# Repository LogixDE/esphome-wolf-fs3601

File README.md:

# ESPHome-Ersatz für den Wolf-Fernversteller FS 3601

Ein **ESP32-C3 mit ESPHome** ersetzt die analoge Fernbedienung **Wolf FS 3601** eines alten Wolf-Gaskessels (hier NG-2E-17, Baujahr 1993). Die Platine bildet den Widerstand zwischen den Kesselklemmen 1 und 2 nach, galvanisch getrennt über PhotoMOS-Relais. Damit kann **Home Assistant** die Heizkurve des Kessels stufenlos und **bedarfsgerecht** nachregeln, abhängig davon, was die einzelnen Räume tatsächlich brauchen.

| Original FS 3601 | Ersatzplatine FS3601-ESP |
|---|---|
|  |  |

## Was drin ist

| Ordner | Inhalt |
|---|---|
| [`docs/`](docs) | Dokumentation, Messwerte, Diagramme |
| [`fs3601/`](fs3601) | Reverse-Engineering der Original-FB: Fotos (nummerierte Lötaugen), Schaltplan |
| [`hardware/`](hardware) | KiCad-Platine, Gerber, Stückliste, Bestückungsdaten, Schaltplan, Generator-Skripte |
| [`firmware/`](firmware) | ESPHome-Konfiguration |
| [`home-assistant/`](home-assistant) | Automationen und Helfer für die bedarfsgerechte Heizkurve |
| [`tools/`](tools) | Hilfsskripte (Bildentzerrung, Diagramme) |

## Dokumentation

1. [Reverse-Engineering der FS 3601](docs/1_reverse_engineering.md): Netzliste, Schalterstellungen, Kennfeld
2. [Hardware](docs/2_hardware.md): Platine, Bestückung, galvanische Trennung, Inbetriebnahme, Kalibrierung
3. [Firmware](docs/3_firmware.md): Betriebsarten, Entitäten, Sicherheit
4. [Home Assistant](docs/4_home_assistant.md): bedarfsgerechte Heizkurve, Kesselschutz, erste Ergebnisse
5. [Messwerte](docs/5_messwerte.md): alle Messungen und Lehrgeld

## Kurzfassung

- Der Kessel misst nur den **Widerstand an Klemme 1–2**. Mit Raumeinfluss 0 erzeugt die FS 3601 Werte von **12,96 kΩ bis 16,30 kΩ** sowie 3,87 kΩ für „Aus“.
- Die Platine stellt **64 Widerstandswerte** von 12,88 bis 16,37 kΩ ein (Raster ≤ 70 Ω), über sechs PhotoMOS-Schließer (TLP240A) an einer Widerstandskette. Ein **PhotoMOS-Öffner** (CPC1117N) brückt K1–K2, wenn der ESP stromlos ist. Dann läuft der Kessel wie ohne Fernbedienung.
- Eigenes Netzteil (HLK-PM01) mit Sicherung und Varistor. Zum Kessel hin ist alles über die PhotoMOS getrennt (Klemme 1 liegt auf N).
- In Home Assistant regelt eine Automation die **Heizkurve 0–100 %** alle 10 Minuten nach Raumdefizit und Ventilstellung der Thermostate. Dazu kommt ein Kesselschutz über die Rücklauftemperatur.

## Warnung

Die Platine arbeitet mit **230 V Netzspannung**, und Klemme 1 des Kessels liegt auf dem Neutralleiter. Aufbau und Anschluss nur durch Personen mit entsprechender Qualifikation, nur spannungsfrei, in einem geschlossenen, flammgeschützten Gehäuse. Eingriffe in die Heizungsanlage geschehen auf eigene Verantwortung. Das Projekt ist ein privater Nachbau und steht in keiner Verbindung zu Wolf.

## Lizenz

Software (Firmware, HA-Automationen, Skripte): **MIT**. Hardware und Doku: **CERN-OHL-P-2.0**. Details in [`LICENSE`](LICENSE) und [`hardware/LICENSE`](hardware/LICENSE).

Kurz: Jeder darf nachbauen, ändern, verkaufen und weitergeben, auch kommerziell, solange der Copyright-Hinweis erhalten bleibt. Es gibt keinerlei Gewährleistung.

## Autor

Fabian Harder

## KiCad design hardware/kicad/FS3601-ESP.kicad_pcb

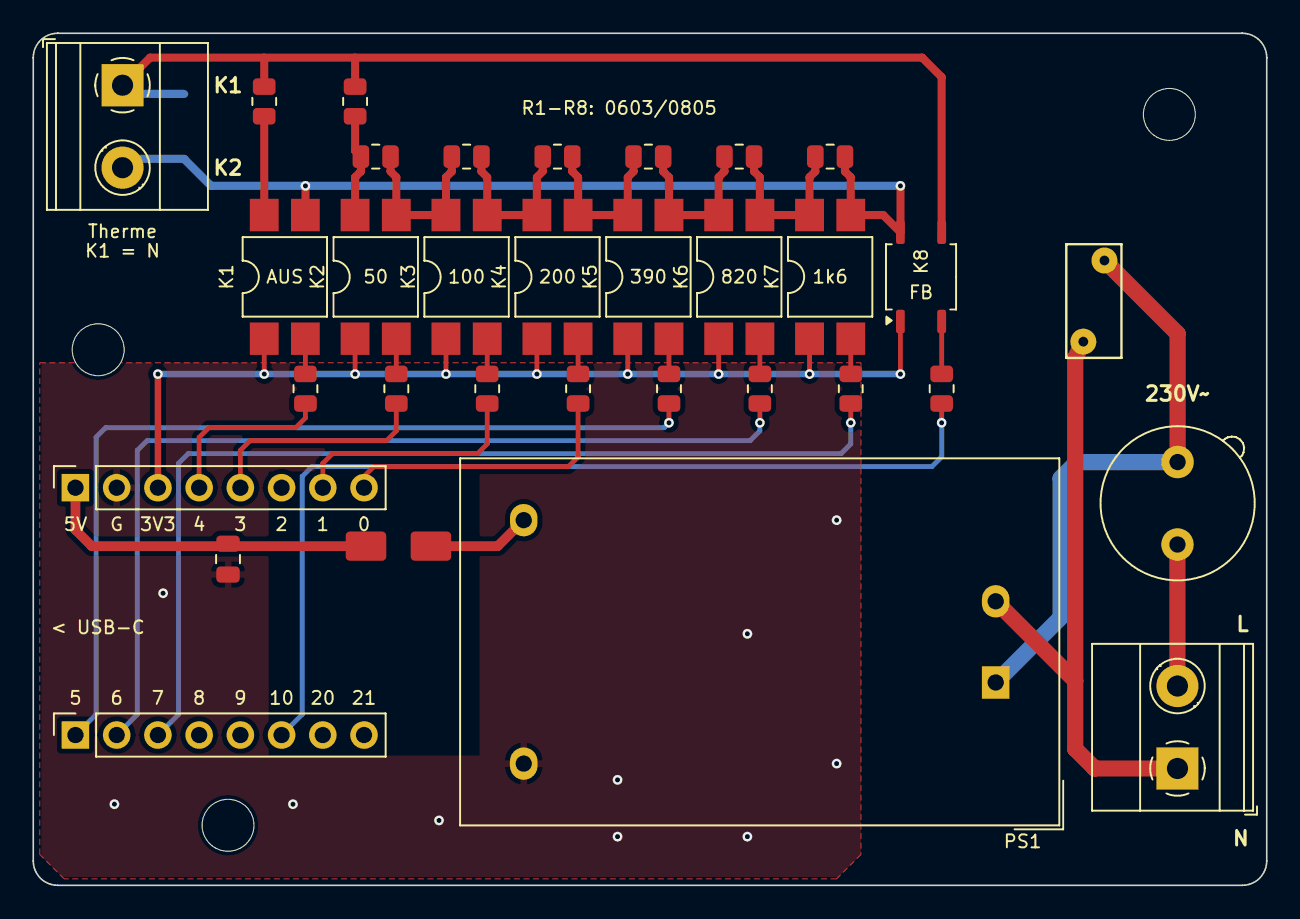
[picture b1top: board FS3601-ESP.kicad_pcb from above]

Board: 2 copper layers, 76.0 x 52.5 mm, 37 parts (1 on the bottom side), 32 nets.

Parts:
C1: 10uF; C_0805_2012Metric
D1: SMAJ12CA; D_SMA
D2: B180; D_SMA
F1: T315mA; Fuseholder_TR5_Littelfuse_No560_No460
H: MountingHole_3.2mm_M3
H#2, H#3: MountingHole_3.2mm_M3
J1, J3: SPTH 1,5/2-5,08; TerminalBlock_Phoenix_MKDS-1,5-2-5.08_1x02_P5.08mm_Horizont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
K1, K2, K3, K4, K5, K6, K7: TLP240A; SMDIP-4_W7.62mm
K8: CPC1117N; SOP-4_3.8x4.1mm_P2.54mm
PS1: HLK-PM01; Converter_ACDC_Hi-Link_HLK-PMxx
R1: 13k0; R_0603_0805_Combo
R2: 49R9; R_0603_0805_Combo
R3: 100R; R_0603_0805_Combo
R4: 200R; R_0603_0805_Combo
R5: 390R; R_0603_0805_Combo
R6: 820R; R_0603_0805_Combo
R7: 1k6; R_0603_0805_Combo
R8: 5k11; R_0603_0805_Combo
R11, R12, R13, R14, R15, R16, R17, R18: 390R; R_0805_2012Metric
RV1: S07K275; RV_Disc_D7mm_W3.4mm_P5mm
U1A: SuperMini A; PinSocket_1x08_P2.54mm_Vertical
U1B: SuperMini B; PinSocket_1x08_P2.54mm_Vertical

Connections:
3V3: K1.1, K2.1, K3.1, K4.1, K5.1, K6.1, K7.1, K8.1, U1A.3
5V: C1.2, D2.1, U1A.1
5V_PS: D2.2, PS1.4
GND: C1.1, PS1.3, U1A.2
K1: D1.1, J1.1, K8.3, R1.2, R8.2
K2: D1.2, J1.2, K1.3, K7.3, K8.4, R7.2
LEDK1: K1.2, R11.2
LEDK2: K2.2, R12.2
LEDK3: K3.2, R13.2
LEDK4: K4.2, R14.2
LEDK5: K5.2, R15.2
LEDK6: K6.2, R16.2
LEDK7: K7.2, R17.2
LEDK8: K8.2, R18.2
L_F: F1.2, PS1.1, RV1.1
L_IN: F1.1, J3.2
N: J3.1, PS1.2, RV1.2
N1: K2.4, R1.1, R2.1
N2: K2.3, K3.4, R2.2, R3.1
N3: K3.3, K4.4, R3.2, R4.1
N4: K4.3, K5.4, R4.2, R5.1
N5: K5.3, K6.4, R5.2, R6.1
N6: K6.3, K7.4, R6.2, R7.1
NAUS: K1.4, R8.1
S1: R11.1, U1A.4
S2: R12.1, U1A.5
S3: R13.1, U1A.7
S4: R14.1, U1A.8
S5: R15.1, U1B.1
S6: R16.1, U1B.2
S7: R17.1, U1B.3
S8: R18.1, U1B.6
